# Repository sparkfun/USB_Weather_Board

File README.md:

# **NOTE: This product has been retired from our catalog. The information contained here is for reference only. No support is guaranteed. For a new version, please check out our [Weather Shield](https://www.sparkfun.com/products/12081).**

*If you are looking for more up-to-date info, please check out some of these resources to see how other users are still hacking and improving on this product.*
* *[SparkFun Forum](https://forum.sparkfun.com/)*
* *[Comments Here on GitHub](https://github.com/sparkfun/USB_Weather_Board/issues)*
* *[IRC Channel](https://www.sparkfun.com/news/263)*

## USB Weather Board [(SEN-10586)](https://www.sparkfun.com/products/10586)

SparkFun's USB Weather Board contains sensors that can be used to monitor atmospheric pressure, humidity, temperature, and light level. The board can also be interfaced to wind speed, direction, and rainfall sensors available separately from Sparkfun.

Product page: [www.sparkfun.com/products/10586](https://www.sparkfun.com/products/10586)

User guide: [https://github.com/sparkfun/USB_Weather\_Board/blob/master/USB\_Weather\_Board\_V3\_datasheet\_130705.pdf?raw=true](https://github.com/sparkfun/USB_Weather_Board/blob/master/USB_Weather_Board_V3_datasheet_130705.pdf?raw=true)

Github repository: [https://github.com/sparkfun/USB\_Weather\_Board](https://github.com/sparkfun/USB_Weather_Board)

This archive contains the latest sketch (firmware) that the USB Weather Board uses to sample the sensors and output data. You can use this sketch as-is, modify it to suit your own purposes, or write your own sketches from scratch. See the datasheet and schematics for more information.

### Installation:

If you haven't, install the free Arduino IDE, available at [www.arduino.cc](http://www.arduino.cc). This code was tested using Arduino versions 1.0.3, 1.0.4 and 1.0.5.

This sketch requires several nonstandard libraries (special device interface code):

* SHT15x by Jonathan Oxer et.al.
* SFE_BMP085 library by SparkFun
	
These libraries are included in this archive, and must be installed onto your computer in order for the code to compile correctly. See the instructions below.

#### Installing the required files:

TL;DR: The one-step procedure to install all of the required files is to drag the contents of the Arduino folder contained in this archive into your personal Arduino sketch folder (this is normally located in your personal documents folder.) This will create a "libraries" folder (containing the above libraries), and a "Weather\_Board\_3" folder containing the sketch.

If there is already a "libraries" folder, add the included libraries to it. If there are older versions of the above libraries in the folder, please replace them with the versions in this archive. If it is running, restart the Arduino IDE to get it to recognize the new libraries.

#### Loading the firmware onto your USB Weather Board:

1. Connect the USB Weather Board to your computer using a standard mini-B USB cable (available everywhere including www.sparkfun.com). Move both switches on the USB Weather Board to USB. The red LED should light up and your computer should automatically install the FTDI drivers and create a virtual COM port. If there is a problem installing the FTDI drivers, please see the instructions at www.arduino.cc.

2. Start the Arduino IDE.

3. Select the following board type from the Tools/Board menu: "Arduino Pro or Pro Mini (3.3V, 8MHz) w/ATmega328"

4. Select the correct serial port from the Tools/Serial Port menu. This will be the port that your FTDI board or cable has created, it is usually the highest numbered port in the list of options.

5. Load (up-arrow button) the weather\_board\_3.ino sketch into the Arduino IDE.

6. Click on the Upload (right arrow) button at the top of the window. The code should compile then upload to the USB Weather Board. If there are any errors, double-check that you installed the required libraries to the correct folder, and have restarted the Arduino IDE. If you continue to have problems, please contact SparkFun Technical Support (see the "Contact" section of www.sparkfun.com) and they'll be happy to help you get up and running.

Once the sketch is uploaded, the green LED will blink three times and the board will begin running. To check the output, you can use the terminal software of your choice, or open the Arduino IDE's Serial Monitor window (magnifying-glass button). Ensure that the Serial Monitor window is set to "9600 baud", and that line ending is set to "carriage return". To bring up the menu, type a 'Z' character into the entry box at the top of the window, and press send or hit return. See the datasheet for more information.

If you have questions, don't hesistate to contact us at techsupport@sparkfun.com.

Have fun!
Your friends at SparkFun.

### Revision history:

1.4 2013/7/5

> Changed all menu operations to completely support Arduino serial monitor (CR/NL ignored unless needed). Set Arduino serial monitor to 9600 baud, and line endings to carriage return.

1.3 2013/6/25

> Added code to prevent an intermittent lockup when rebooting; now resets the humidity sensor connection before intializing the BMP085. Many thanks to Nathan Isherwood.
		
> Added plain 'Z' and 'z' as well as CTRL-Z to enter menu to better support Arduino serial monitor.
		
> Fixed error in rain-gauge constant. Many thanks to Michael Bauer.

> Added reset to factory defaults option to menu.

> Moved constant strings to flash (freed over 1K bytes!)

1.2 2012/1/23

> Update all code to be compatible with Arduino 1.0
		
1.1 2011/08/01

> Changed sample_rate to 32-bit, max = 4294966 seconds (47 days)

> RAM is also getting tight, so removed some error strings and added RAM gauge to menu.
		
1.0 2011/06/27

> Initial release

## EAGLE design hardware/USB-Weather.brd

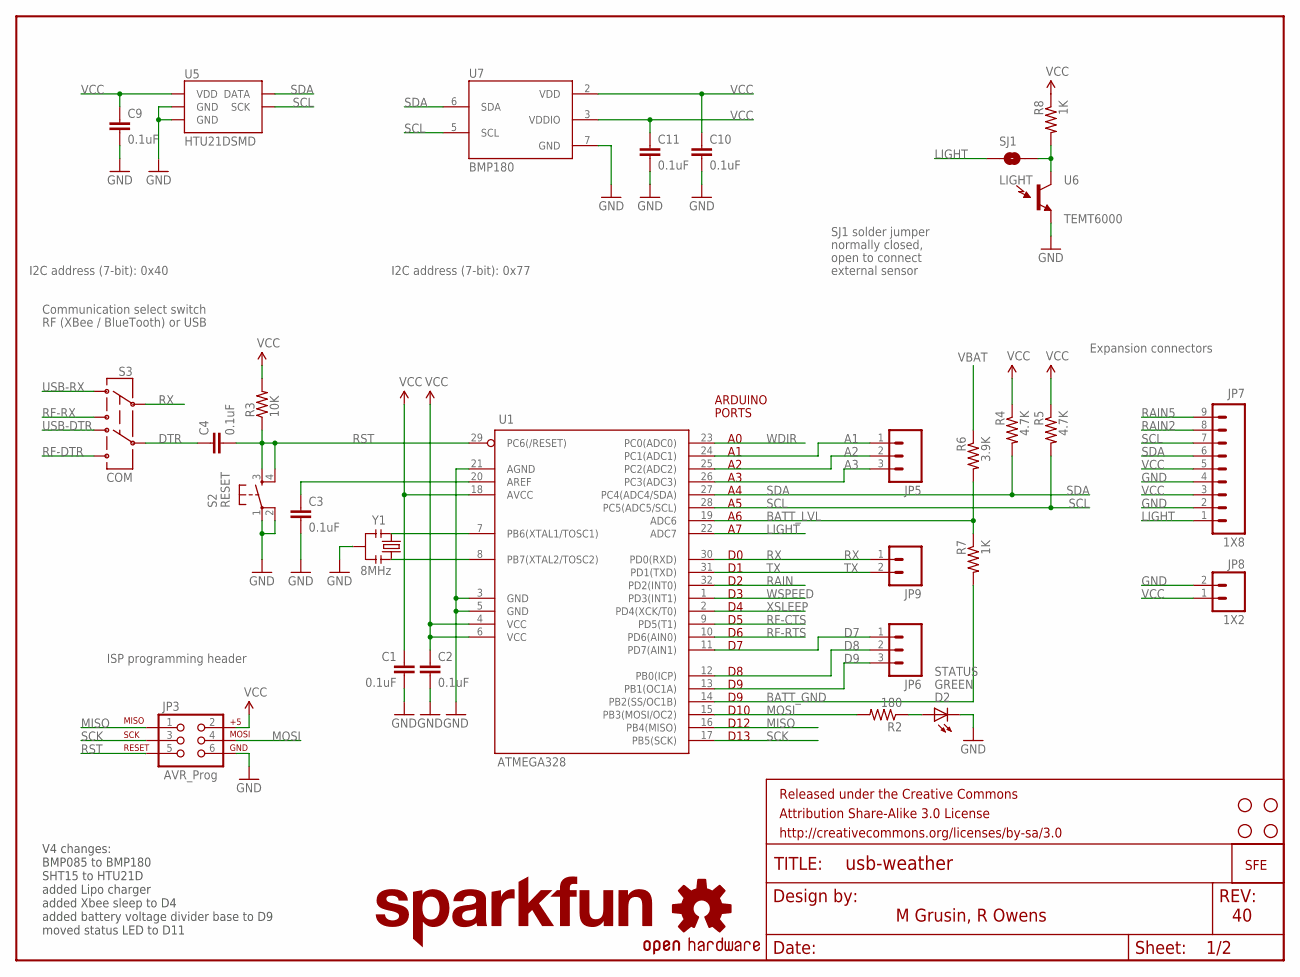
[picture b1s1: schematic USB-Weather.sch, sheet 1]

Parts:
C1, C2, C3, C4, C9, C10, C11: 0.1uF; 0603-CAP
D2: GREEN; LED-0603
FRAME3: FRAME-LETTER; CREATIVE_COMMONS
JP3: AVR_Prog; 2X3
JP5, JP6: M03_ROUND_ONLY_NO_SILK; 1X03_ROUND_ONLY_NO_SILK
JP7: 1X8; 1X09
JP8: 1X2; 1X02_NO_SILK
JP9: M021X02_NO_SILK; 1X02_NO_SILK
LOGO1: LOGO-SFENEW; SFE-NEW-WEBLOGO
LOGO2: OSHW-LOGOS; OSHW-LOGO-S
LOGO3: SFE_LOGO_NAME.1_INCH; SFE_LOGO_NAME_.1
R2: 180; 0603-RES
R3: 10K; 0603-RES
R4, R5: 4.7K; 0603-RES
R6: 3.9K; 0603-RES
R7, R8: 1K; 0603-RES
S2: RESET; TACTILE_SWITCH_SMD
S3: COM; AYZ0202
SJ1: LIGHT; SJ_2S
U1: ATMEGA328; TQFP32-08
U5: HTU21DSMD; HTU21D
U6: TEMT6000; TEMT6000-SEN
U7: BMP180
U$2, U$3, U$4, U$5: STAND-OFF
Y1: 8MHz; RESONATOR-SMD

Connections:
A1: JP5.1, U1.24 (PC1(ADC1))
A2: JP5.2, U1.25 (PC2(ADC2))
A3: JP5.3, U1.26 (PC3(ADC3))
BATT_GND: R7.2, U1.14 (PB2(SS/OC1B))
BATT_LVL: R6.2, R7.1, U1.19 (ADC6)
D7: JP6.1, U1.11 (PD7(AIN1))
D8: JP6.2, U1.12 (PB0(ICP))
D9: JP6.3, U1.13 (PB1(OC1A))
DTR: C4.1, S3.5
GND: C1.2, C2.2, C3.2, C9.2, C10.2, C11.2, D2.C, JP3.6, JP7.2, JP7.4, JP8.2, S2.1, S2.2, U1.3 (GND), U1.5 (GND), U1.21 (AGND), U5.7 (GND), U5.GND, U6.EMITTER (E1), U7.7 (GND), Y1.2; also elsewhere on the board
LIGHT: JP7.1, SJ1.1, U1.22 (ADC7)
MISO: JP3.1, U1.16 (PB4(MISO))
MOSI: JP3.4, R2.2, U1.15 (PB3(MOSI/OC2))
unnamed: D2.A, R2.1
unnamed: C3.1, U1.20 (AREF)
unnamed: R8.2, SJ1.2, U6.COLLECTOR (C1)
unnamed: U1.7 (PB6(XTAL1/TOSC1)), Y1.1
unnamed: U1.8 (PB7(XTAL2/TOSC2)), Y1.3
RAIN: U1.32 (PD2(INT0)); also elsewhere on the board
RAIN2: JP7.8; also elsewhere on the board
RAIN5: JP7.9; also elsewhere on the board
RF-CTS: U1.9 (PD5(T1)); also elsewhere on the board
RF-DTR: S3.6; also elsewhere on the board
RF-RTS: U1.10 (PD6(AIN0)); also elsewhere on the board
RF-RX: S3.3; also elsewhere on the board
RST: C4.2, JP3.5, R3.1, S2.3, S2.4, U1.29 (PC6(/RESET))
RX: JP9.1, S3.2, U1.30 (PD0(RXD))
SCK: JP3.3, U1.17 (PB5(SCK))
SCL: JP7.7, R5.2, U1.28 (PC5(ADC5/SCL)), U5.SCK, U7.5 (SCL)
SDA: JP7.6, R4.2, U1.27 (PC4(ADC4/SDA)), U5.DATA, U7.6 (SDA)
TX: JP9.2, U1.31 (PD1(TXD)); also elsewhere on the board
USB-DTR: S3.4; also elsewhere on the board
USB-RX: S3.1; also elsewhere on the board
VBAT: R6.1; also elsewhere on the board
VCC: C1.1, C2.1, C9.1, C10.1, C11.1, JP3.2, JP7.3, JP7.5, JP8.1, R3.2, R4.1, R5.1, R8.1, U1.4 (VCC), U1.6 (VCC), U1.18 (AVCC), U5.VDD, U7.2 (VDD), U7.3 (VDDIO); also elsewhere on the board
WDIR: U1.23 (PC0(ADC0)); also elsewhere on the board
WSPEED: U1.1 (PD3(INT1)); also elsewhere on the board
XSLEEP: U1.2 (PD4(XCK/T0)); also elsewhere on the board

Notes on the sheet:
STATUS
SJ1 solder jumper
normally closed,
open to connect
external sensor
Communication select switch
RF (XBee / BlueTooth) or USB
Expansion connectors
I2C address (7-bit): 0x77
I2C address (7-bit): 0x40
ISP programming header
D10
D12
D13
ARDUINO
PORTS
V4 changes: BMP085 to BMP180 SHT15 to HTU21D added Lipo charger added Xbee sleep to D4 added battery voltage divider base to D9 moved status LED to D11
M Grusin, R Owens

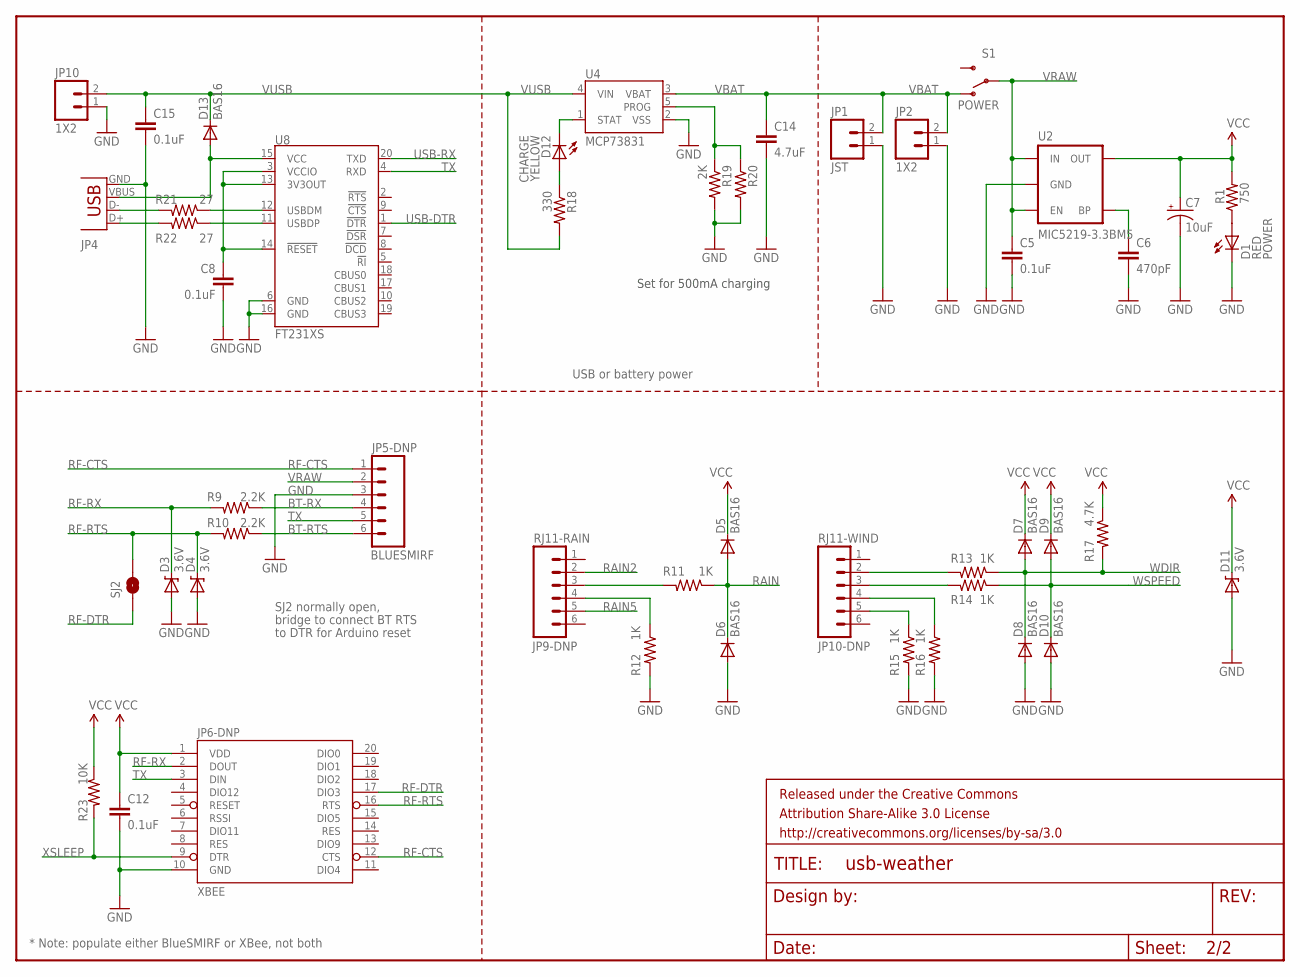
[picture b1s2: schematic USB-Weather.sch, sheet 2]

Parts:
C5, C8, C12, C15: 0.1uF; 0603-CAP
C6: 470pF; 0603-CAP
C7: 10uF; EIA3216
C14: 4.7uF; 0603-CAP
D1: RED; LED-0603
D3, D4, D11: 3.6V; SOD-323
D5, D6, D7, D8, D9, D10, D13: BAS16; SOD-323
D12: YELLOW; LED-0603
FRAME1: FRAME-LETTER; CREATIVE_COMMONS
JP1: JST; JST-2-SMD
JP2, JP10: 1X2; 1X02_NO_SILK
JP4: USBSMD; USB-MINIB
JP5-DNP: BLUESMIRF; 1X06
JP6-DNP: XBEE; XBEE-1
JP9-DNP: RJ11-RAIN; RJ11-6
JP10-DNP: RJ11-WIND; RJ11-6
R1: 750; 0603-RES
R9, R10: 2.2K; 0603-RES
R11, R12, R13, R14, R15, R16: 1K; 0603-RES
R17: 4.7K; 0603-RES
R18: 330; 0603-RES
R19: 2K; 0603-RES
R20: RESISTORPTH-1/6W; 1/6W-RES
R21, R22: 27; 0603-RES
R23: 10K; 0603-RES
S1: POWER; AYZ0202
SJ2: SOLDERJUMPERNO; SJ_2S-NO
U2: MIC5219-3.3BM5; SOT23-5
U4: MCP73831; SOT23-5
U8: FT231XS; SSOP20_L

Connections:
BT-RTS: JP5-DNP.6, R10.1
BT-RX: JP5-DNP.4, R9.1
GND: C5.2, C6.2, C7.C (-), C8.2, C12.2, C14.2, C15.2, D1.C, D3.2 (A), D4.2 (A), D6.2 (A), D8.2 (A), D10.2 (A), D11.2 (A), JP1.1, JP2.1, JP4.GND, JP5-DNP.3, JP6-DNP.10 (GND), JP10.1, R12.2, R15.2, R16.2, R19.2, R20.2, U2.2 (GND), U4.2 (VSS), U8.6 (GND), U8.16 (GND); also elsewhere on the board
unnamed: D1.A, R1.1
unnamed: JP10-DNP.2, R13.2
unnamed: JP10-DNP.3, R14.2
unnamed: C6.1, U2.4 (BP)
unnamed: JP9-DNP.3, R11.2
unnamed: JP9-DNP.4, R12.1
unnamed: JP10-DNP.5, R15.1
unnamed: JP10-DNP.4, R16.1
unnamed: D12.A, R18.1
unnamed: JP4.D-, R21.2
unnamed: JP4.D+, R22.2
unnamed: D13.2 (A), JP4.VBUS, U8.15 (VCC)
unnamed: C8.1, U8.3 (VCCIO), U8.13 (3V3OUT), U8.14 (!RESET)
PROG: R19.1, R20.1, U4.5 (PROG)
RAIN: D5.2 (A), D6.1 (C), R11.1; also elsewhere on the board
RAIN2: JP9-DNP.2; also elsewhere on the board
RAIN5: JP9-DNP.5; also elsewhere on the board
RF-CTS: JP5-DNP.1, JP6-DNP.12 (CTS); also elsewhere on the board
RF-DTR: JP6-DNP.17 (DIO3), SJ2.1; also elsewhere on the board
RF-RTS: D4.1 (C), JP6-DNP.16 (RTS), R10.2, SJ2.2; also elsewhere on the board
RF-RX: D3.1 (C), JP6-DNP.2 (DOUT), R9.2; also elsewhere on the board
STAT: D12.C, U4.1 (STAT)
TX: JP5-DNP.5, JP6-DNP.3 (DIN), U8.4 (RXD); also elsewhere on the board
USB-DTR: U8.1 (!DTR); also elsewhere on the board
USB-RX: U8.20 (TXD); also elsewhere on the board
USB_D+: R22.1, U8.11 (USBDP)
USB_D-: R21.1, U8.12 (USBDM)
VBAT: C14.1, JP1.2, JP2.2, S1.1 (O), U4.3 (VBAT); also elsewhere on the board
VCC: C7.A (+), C12.1, D5.1 (C), D7.1 (C), D9.1 (C), D11.1 (C), JP6-DNP.1 (VDD), R1.2, R17.1, R23.1, U2.5 (OUT); also elsewhere on the board
VRAW: C5.1, JP5-DNP.2, S1.2, U2.1 (IN), U2.3 (EN)
VUSB: C15.1, D13.1 (C), JP10.2, R18.2, U4.4 (VIN)
WDIR: D7.2 (A), D8.1 (C), R13.1, R17.2; also elsewhere on the board
WSPEED: D9.2 (A), D10.1 (C), R14.1; also elsewhere on the board
XSLEEP: JP6-DNP.9 (DTR), R23.2; also elsewhere on the board

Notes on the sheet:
POWER
* Note: populate either BlueSMIRF or XBee, not both
JP4
USB or battery power
SJ2 normally open,
bridge to connect BT RTS
to DTR for Arduino reset
Set for 500mA charging
CHARGE

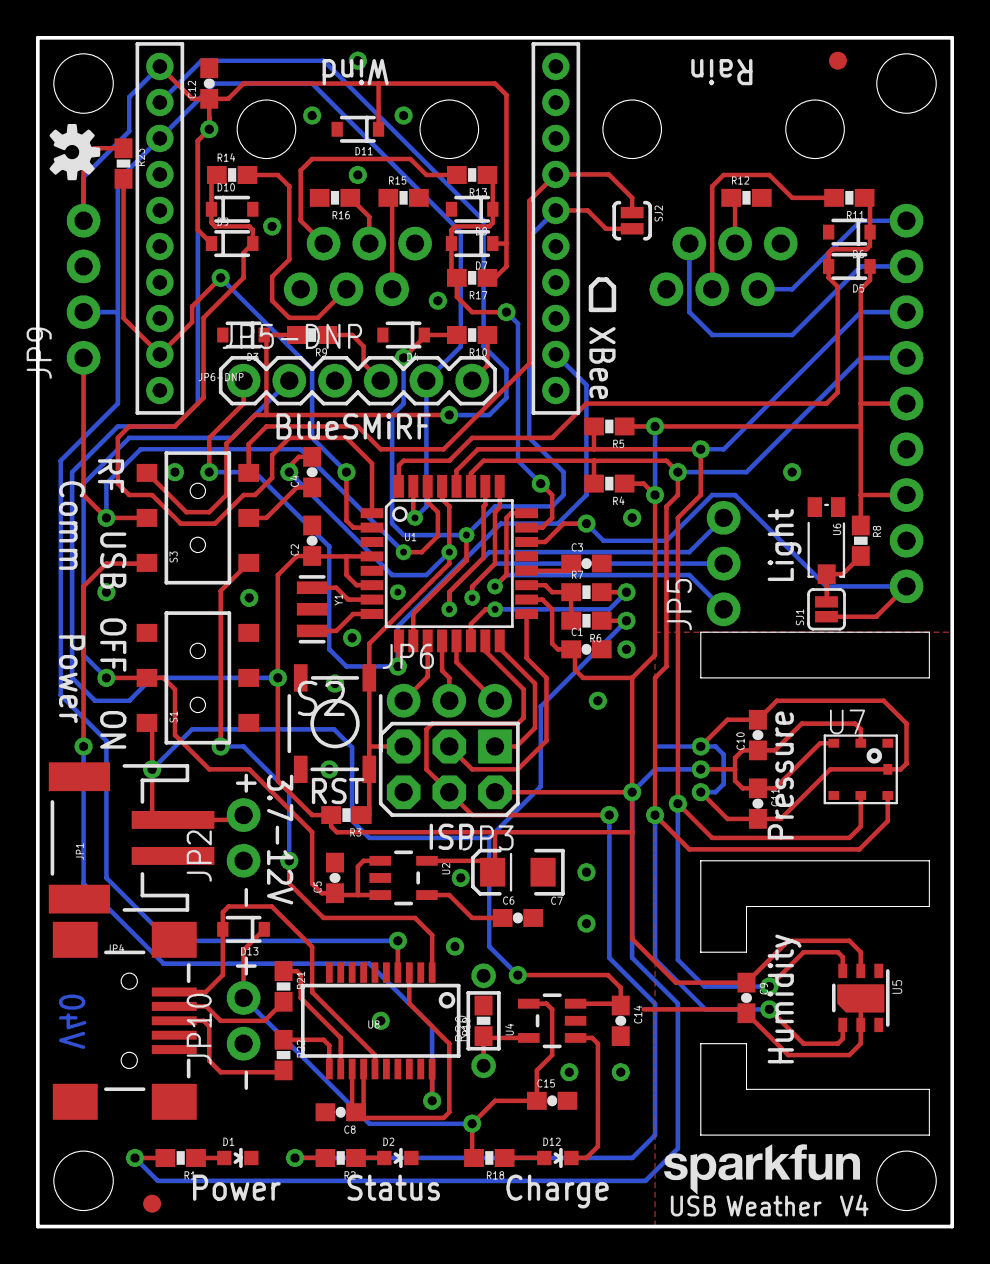
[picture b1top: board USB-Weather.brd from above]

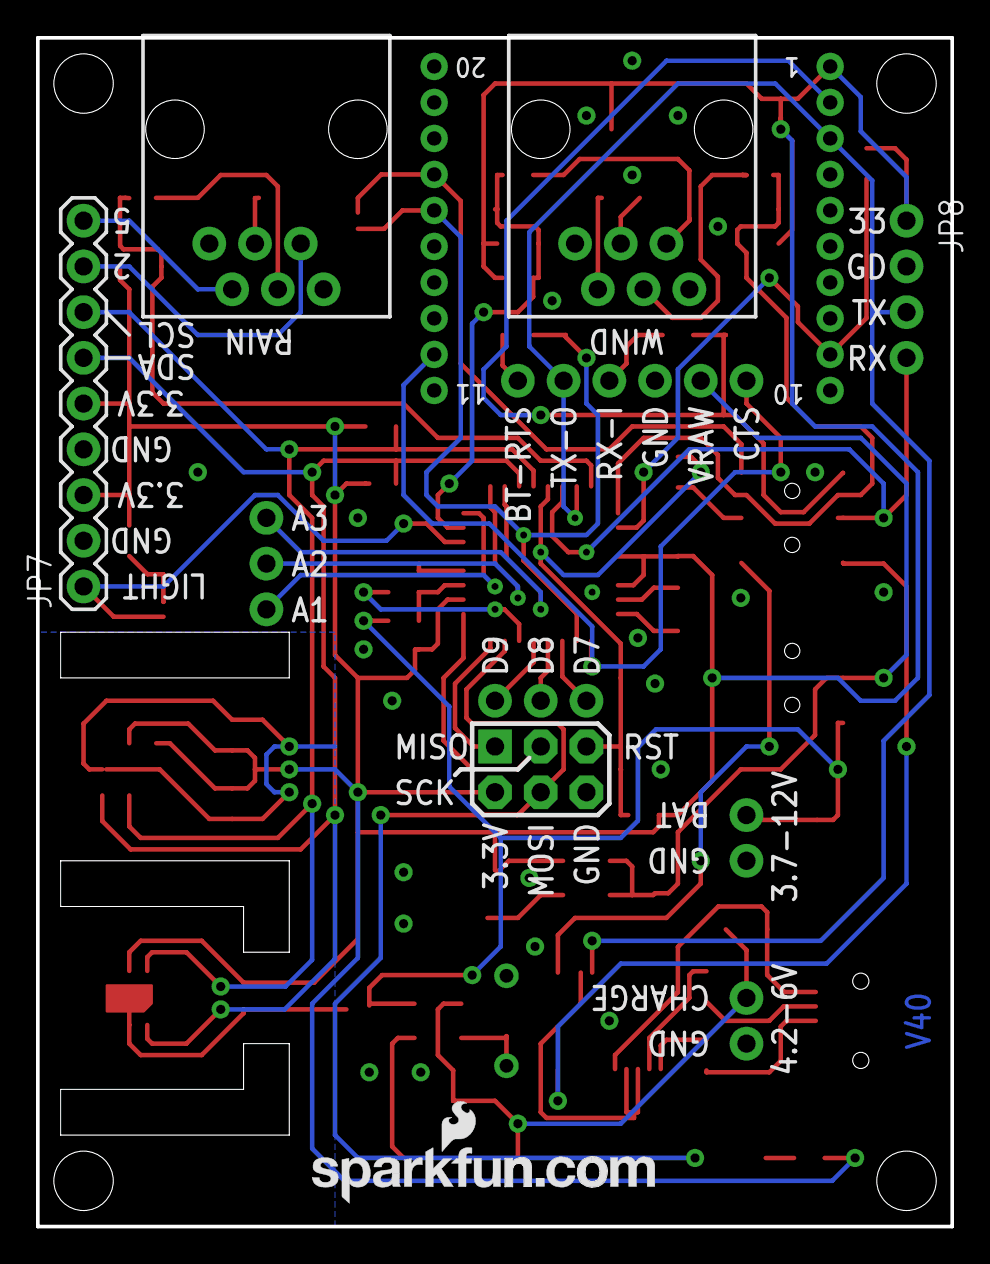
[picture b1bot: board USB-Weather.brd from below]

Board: 2 copper layers, 50.8 x 66.0 mm, 88 parts (5 on the bottom side), 59 nets.

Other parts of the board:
E$1, E$2: FIDUCIAL-1X2

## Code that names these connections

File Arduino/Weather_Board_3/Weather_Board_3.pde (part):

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const int RF_RTS = 6;
const int RF_CTS = 5;
const int STATUSLED = 4;
const int WSPEED = 3;
const int RAIN = 2;

// analog I/O pins
const int LIGHT = 7;
const int BATT_LVL = 6;
const int WDIR = 0;

// global variables
float SHT15_humidity;
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volatile unsigned long raintime, rainlast, raininterval, rain;

// constant conversion factors
const int BATT_RATIO = 63.3271; // divide ADC from BATT_LVL by this to get volts
const float WIND_RPM_TO_MPH = 22.686745; // divide RPM by this for velocity
const float WIND_RPM_TO_MPS = 50.748803; // divide RPM by this for meters per second
const float RAIN_BUCKETS_TO_INCHES = 0.0086206896; // multiply bucket tips by this for inches
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const int LCD = 3; // directly drive a SparkFun serial-enabled 16x2 LCD display

// general units
const int ENGLISH = 1; // wind speed in miles per hour, rain in inches, temperature in degrees Fahrenheit
const int SI = 2; // International System, aka the metric system. Wind speed in meters per second, rain in mm, temperature in degrees Celsius

// pressure units
const int MBAR = 1; // millibars
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  
  pinMode(STATUSLED,OUTPUT); // output to status LED
  
  pinMode(WSPEED,INPUT); // input from wind meters windspeed sensor
  digitalWrite(WSPEED,HIGH); // turn on pullup
  
  pinMode(RAIN,INPUT); // input from wind meters rain gauge sensor
  digitalWrite(RAIN,HIGH); // turn on pullup

  // get settings from EEPROM (use defaults if EEPROM has not been used)
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        break;

      case '8':
        rain = 0;
        Serial.println("Rain counter zeroed");
        Serial.println();
        break;
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
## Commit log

2013-06-26 Initial commit, hardware V31, firmware V12
2013-06-27 Multiple changes to firmware V1.3
    Fix for intermittent lockup on startup (Isherwood)
    Fixed error in rain gauge constant (Bauer)
    Additional characters to get to menu (Z,z,CTRL-Z) to better support
    Arduino serial monitor (no CTRL chars).
    Changed extension from .pde to .ino
    Updated readmes and datasheet
2013-07-01 Initial testing and bug fixes
    Reset issue has not reappeared (report if it does)
    Added 'R' menu option to Reset to factory defaults
    (does not automatically save values to EEPROM, can
    Save afterwards if desired)
    Placed all string constants in Flash, saved 1K RAM!
2013-07-01 minor readme edits
2013-07-03 Updated datasheet for V13
2013-07-03 Minor edits to datasheet
2013-07-05 Firmware V1.4
    Now completely compatible with the Arduino IDE's Serial Monitor window.
    (Ignores unneeded CR/LF characters). Be sure to set Serial Monitor
    window line ending to "carriage return" (dropdown option at bottom of
    window).
2013-07-10 Cleaned up readme.md
2014-01-03 Initial commit for V4
    BMP085 to BMP180
    SHT15 to HTU21D
    (FT232 to FT231)
    (break out all MPU pins)
    (battery charger)
2014-01-04 revision in progress
2014-01-06 pre-review
2014-01-10 Minor updates for reveiw
2017-02-08 Adding note about product retirement to readme.
2017-02-08 Increasing retirement note size.

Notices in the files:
Arduino/Weather_Board_3/Weather_Board_3.pde:
License:
This code is free to use, change, improve, even sell!  All we ask for is two things:
1. That you give SparkFun credit for the original code,
2. If you sell or give it away, you do so under the same license so others can do the same thing.
More at http://creativecommons.org/licenses/by-sa/3.0
parts and their libraries:
SparkFun-Sensors: Licensing: CC v3.0 Share-Alike You are welcome to use this library for commercial purposes.
SparkFun-Aesthetics: Released under the Creative Commons Attribution Share-Alike 3.0 License
